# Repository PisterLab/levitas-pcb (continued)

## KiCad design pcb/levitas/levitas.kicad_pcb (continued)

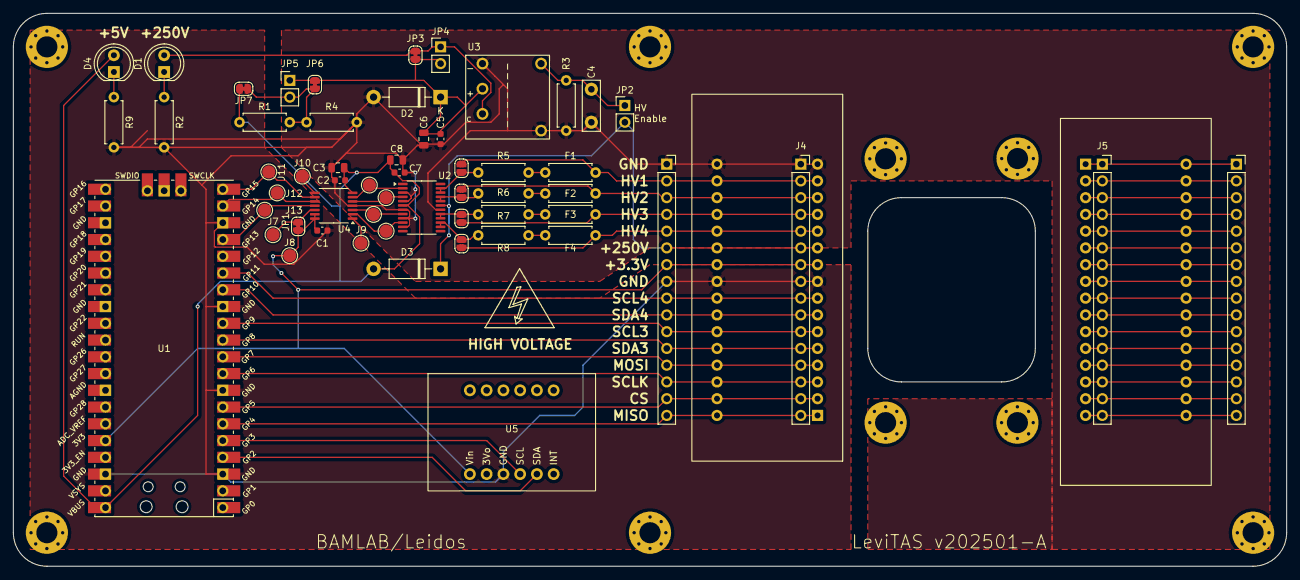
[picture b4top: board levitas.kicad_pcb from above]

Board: 2 copper layers, 193.0 x 83.8 mm, 58 parts (0 on the bottom side), 58 nets.

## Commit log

2025-01-23 Add Pico SDK
2025-01-23 Ignore build files
2025-01-27 Serial print demo for 20250123 assembled board
2025-01-27 MPU-6050 accelerometer demo works
2025-01-28 Enable Pico board 3.3V bus PWM mode for low noise
2025-01-31 SPI communication to DAC works
2025-02-03 Control DACs separately
2025-02-10 FDC2112 capacitive sensor I2C working
2025-02-12 FDC2112 data reading working
2025-02-12 Two FDC2112 sensors working simultaneously
2025-02-18 Basic PIO compilation working
2025-02-21 Have 4 FDC2112 chips working at once via PIO I2C
2025-02-22 Remove autopush disable (and race conditions)
2025-02-22 Clarify PIO FIFO algorithms
2025-02-27 I2C write finally works properly
2025-02-27 PIO I2C read/write now both fully working
2025-02-27 4-way parallel I2C write works
2025-02-27 PIO I2C 4-way read/write all works!
2025-02-27 Fix minor typo in I2C parallel read function
2025-02-27 Increase I2C to 400kHz, enable clock stretch
2025-02-27 Remove test files
2025-02-28 Moved USB printf to second core
2025-02-28 Multicore printing with low frequency drift
2025-03-10 Capacitor sensor readout and plotting working
2025-03-10 Rearrange test files
2025-03-10 Refine test MPU6050 accelerometer code
2025-03-10 Refine test fdc2112 pio code
2025-03-10 Refine test fdc2112 code
2025-03-10 Refine MAX5715 HVAWG test code
2025-03-10 Combine capacitance sensing and high voltage
2025-03-11 Clean repo
2025-03-11 Move firmware folder
2025-03-11 Add datasheets
2025-03-11 Add readme
2025-03-11 Add PCB files
2025-03-11 Add enclosure files
2025-03-11 Add pictures
2025-03-11 Update PCB files to KiCad 9
2025-03-11 Try fixing KiCad 9 bug
2025-03-13 Add initial software instructions
2025-03-14 i am testing git commit with test
2025-03-14 now i delete test
2025-03-18 This is the daughter board version 2 with no capacitance sensors
2025-03-18 This is the design for the daughter board without capacitance sensors
2025-03-19 v2 without copper layer, without capacitance sensors
2025-03-20 Add high voltage code and extra commentary
2025-03-20 Clarify PIO I2C library edits
2025-03-20 Add configuration to allow compiling with VS Code
2025-03-20 Clarify Pico SDK import
2025-03-20 Update VS Code configuration instructions
2025-03-20 Clarify USB communication prerequisites
2025-03-20 Clarify CMakeLists.txt update protocol
2025-03-20 Summarize installation instructions
2025-03-20 Notes on firmware files
2025-03-20 Clarify documentation links
2025-03-20 Update firmware documentation
2025-03-20 Add notes on microcontroller choice
2025-03-20 Add data collection scripts
2025-03-20 Don't save recorded data
2025-03-20 Typo fix
2025-04-15 adapter pcb to connect MEMS breakout board to motherboard
2025-05-24 updated adapter-pcb + gerber zip files(need yichen to review)
